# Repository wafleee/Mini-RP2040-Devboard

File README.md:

# Mini RP2040 Devboard

I made a mini devboard that uses the RP2040 as the MCU. It is slightly bigger than the XIAO esp32 s3 but it features 4 extra pins

# Features 
1. ESD protection(protection against electrostatic discharge from body )
2.  Dual-core Arm Cortex-M0+ running up to 133 MHz
3.  18 GPIO pins| 3 ADC pins| GPIO 4- SDA | GPIO 5 - SCL
4.  

# SCHEMATIC

# PCB

# Firmware

No firmware is needed, just hit upload to any sketch on Arduino IDE and it will built itself.

#BOM

| Designator                                     | Footprint                                               | Qty | Value                       | Link                                                                                                                                                               |
| ---------------------------------------------- | ------------------------------------------------------- | --- | --------------------------- | ------------------------------------------------------------------------------------------------------------------------------------------------------------------ |
| C10, C12, C13, C14, C15, C16, C17, C19, C3, C9 | 603                                                     | 10  | 100nF                       | Already owned                                                                                                                                                      |
| C11, C18, C7, C8                               | 603                                                     | 4   | 1µF                         | [Robu](https://robu.in/product/06033d105kat2a-kyocera-avx-cap-smd-mlcc-1-%c2%b5f-25-v-0603-pack-of-1/)                                                             |
| C4, C5                                         | 603                                                     | 2   | 15pF                        | [Robu](https://robu.in/product/0603n150j500ct-walsin-cap-smd-mlcc-15-pf-50-v-0603-pack-of-10/)                                                                     |
| C6                                             | 805                                                     | 1   | 10µF                        | [Robu](https://robu.in/product/cc0805kkx5r8bb106-yageo-cap-smd-mlcc-10-%c2%b5f-25-v-0805-2012-metric10-x5r-cc-series/)                                             |
| D1                                             | LED_WS2812B-2020_PLCC4_2.0x2.0mm                        | 1   | WS2812B-2020                | [Robu](https://robu.in/product/sme-ws2812b-2020-addressable-rgb-pixel-led-worldsemi/)                                                                                                                                                                 |
| D2                                             | 603                                                     | 1   | LED                         | [Robu](https://robu.in/product/19-217-r6c-al1m2vy-3t-everlight-red-528nm-led-indication-discrete-3-3v-0603-1608-metric/)                                           |
| J1                                             | USB_C_Receptacle_GCT_USB4105-xx-A_16P_TopMnt_Horizontal | 1   | USB_C_Receptacle_USB2.0_14P | [Robu](https://robu.in/product/type-c-31-m-12-hroparts-5a-1-16p-female-type-c-smd-usb-connectors-rohs/)                                                            |
| J4, J5                                         | PinHeader_1x10_P2.54mm_Vertical                         | 2   | Conn_01x10_Pin              | [Robu](https://robu.in/product/ds1021-1x10sf11-b-connfly-1x10-pin-2-54mm-pin-header-v-t-type/)                                                                     |
| R1, R2                                         | 603                                                     | 2   | 5.1kΩ                       | [Robu](https://robu.in/product/rt0603fre075k1l-yageo-100mw-thin-film-resistor-75v-%c2%b150ppm-%e2%84%83-%c2%b11-5-1k%cf%89-0603-chip-resistor-surface-mount-rohs/) |
| R3, R6                                         | 603                                                     | 2   | 1kΩ                         | [Robu](https://robu.in/product/1k-ohm-1-4w-0603-surface-mount-chip-resistor-pack-of-100/)                                                                          |
| R4, R5                                         | 603                                                     | 2   | 27Ω                         | [Robu](https://robu.in/product/rc0603jr-0727rl-yageo-smd-chip-resistor-27-ohm-%c2%b1-5-100-mw-0603-1608-metric-thick-film-general-purpose/)                        |
| SW1                                            | SW_SPST_B3U-1000P                                       | 1   | SW_MEC_5G                   | [Robu](https://robu.in/product/1-month-warranty-470/)                                                                                                              |
| U1                                             | QFN-56-1EP_7x7mm_P0.4mm_EP3.2x3.2mm                     | 1   | RP2040                      | [Robu](https://robu.in/product/raspberry-pi-rp2040/)                                                                                                               |
| U3                                             | SOIC-8_5.3x5.3mm_P1.27mm                                | 1   | W25Q128JVS                  | [Lion Circuits](https://www.lioncircuits.com/parts/W25Q128JVSIQ)                                                                                                   |
| U4                                             | SOT-23-5                                                | 1   | AP2112K-3.3                 | [Lion Circuits](https://www.lioncircuits.com/parts/AP2112K-3.3TRG1)                                                                                                |
| U5                                             | SOT-23-6                                                | 1   | USBLC6-2SC6                 | [Robu](https://robu.in/product/usblc6-2sc6-ms-msksemi-4-5a-15v-150w-6v-5v-sot-23-6-esd-and-surge-protection-tvs-esd-rohs/)                                         |
| Y2                                             | Crystal_SMD_Abracon_ABM8AIG-4Pin_3.2x2.5mm              | 1   | Crystal_GND3                | [Robu](https://robu.in/product/cm4012m00008001-huaxindianzi/)                                                                                                      |

# Credits
Kicad - https://www.kicad.org/

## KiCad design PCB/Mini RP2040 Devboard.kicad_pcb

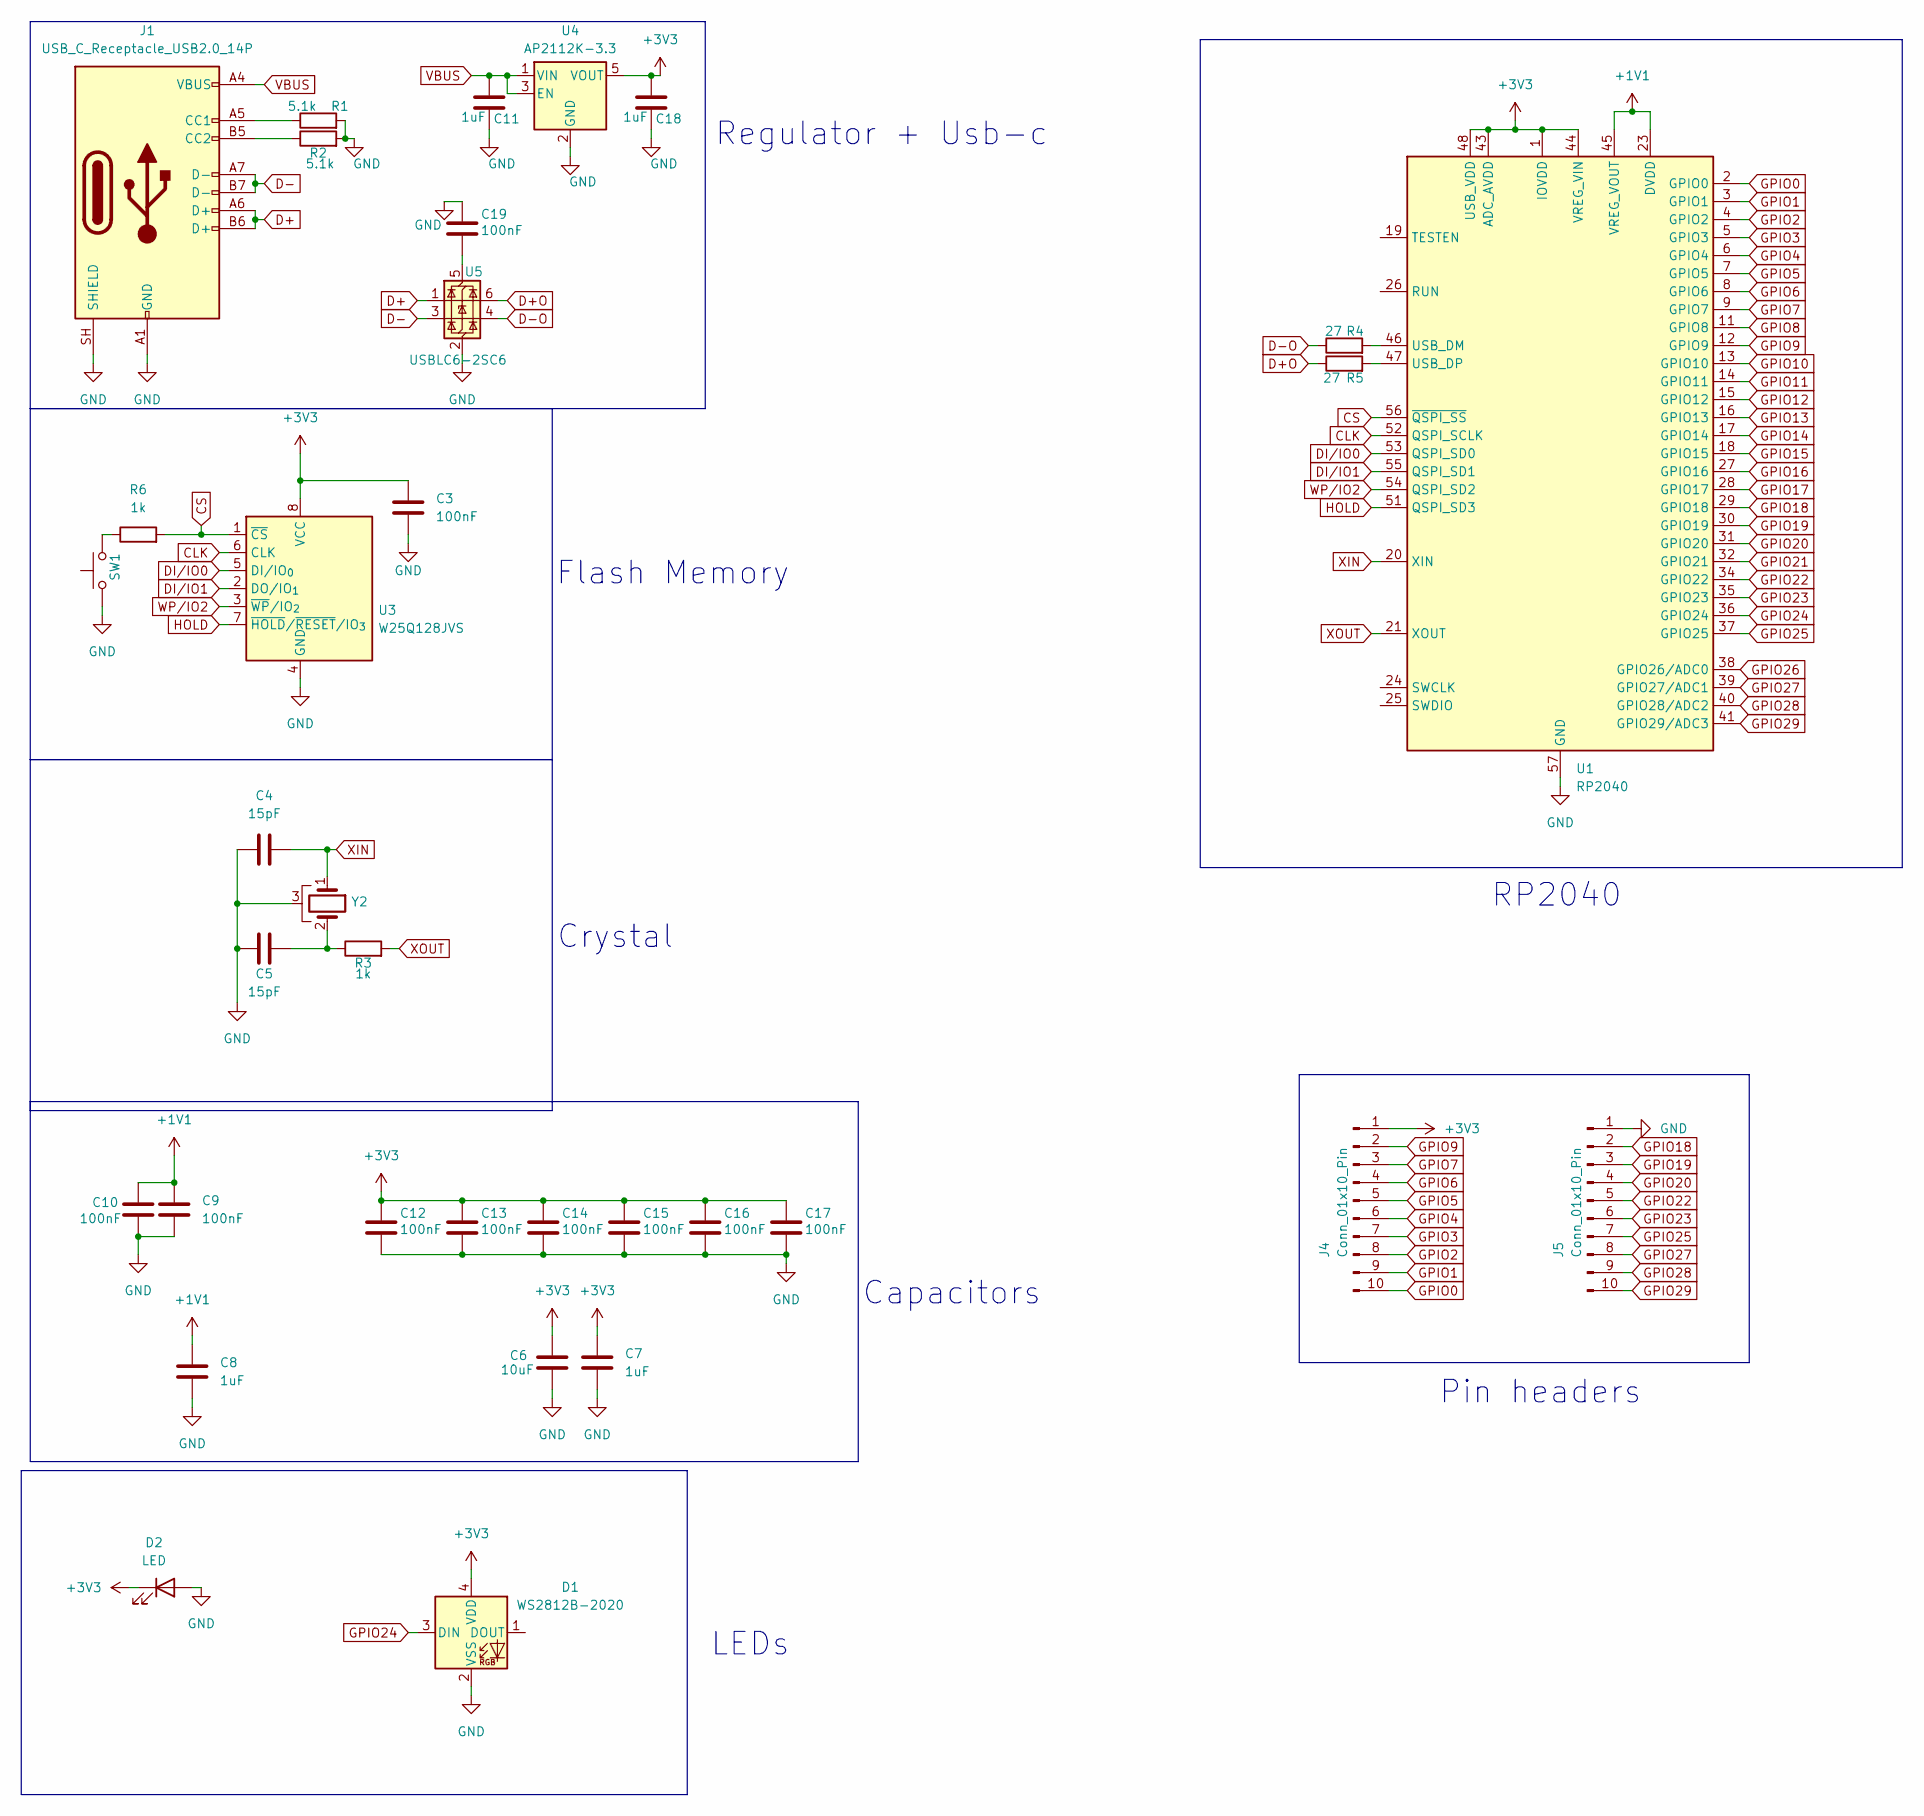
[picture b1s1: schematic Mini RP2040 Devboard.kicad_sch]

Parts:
C3, C9, C10, C12, C13, C14, C15, C16, C17, C19: 100nF; C_0603_1608Metric
C4, C5: 15pF; C_0603_1608Metric
C6: 10uF; C_0805_2012Metric
C7, C8, C11, C18: 1uF; C_0603_1608Metric
D1: WS2812B-2020; LED_WS2812B-2020_PLCC4_2.0x2.0mm
D2: LED; LED_0603_1608Metric
J1: USB_C_Receptacle_USB2.0_14P; USB_C_Receptacle_GCT_USB4105-xx-A_16P_TopMnt_Horizontal
J4, J5: Conn_01x10_Pin; PinHeader_1x10_P2.54mm_Vertical
R1, R2: 5.1k; R_0603_1608Metric
R3, R6: 1k; R_0603_1608Metric
R4, R5: 27; R_0603_1608Metric
SW1: SW_MEC_5G; SW_SPST_B3U-1000P
U1: RP2040; QFN-56-1EP_7x7mm_P0.4mm_EP3.2x3.2mm
U3: W25Q128JVS; SOIC-8_5.3x5.3mm_P1.27mm
U4: AP2112K-3.3; SOT-23-5
U5: USBLC6-2SC6; SOT-23-6
Y2: Crystal_GND3; Crystal_SMD_Abracon_ABM10-4Pin_2.5x2.0mm

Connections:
+1V1: C8.1, C9.1, C10.1, U1.23 (DVDD), U1.45 (VREG_VOUT), U1.50 (DVDD)
+3V3: C3.1, C6.1, C7.1, C12.1, C13.1, C14.1, C15.1, C16.1, C17.1, C18.1, D1.4 (VDD), D2.1 (K), J4.1, U1.1 (IOVDD), U1.10 (IOVDD), U1.22 (IOVDD), U1.33 (IOVDD), U1.42 (IOVDD), U1.43 (ADC_AVDD), U1.44 (VREG_VIN), U1.48 (USB_VDD), U1.49 (IOVDD), U3.8 (VCC), U4.5 (VOUT)
CLK: U1.52 (QSPI_SCLK), U3.6 (CLK)
CS: R6.2, U1.56 (~QSPI_SS), U3.1 (~CS)
D+: J1.A6 (D+), J1.B6 (D+), U5.1 (I/O1)
D+O: R5.1, U5.6 (I/O1)
D-: J1.A7 (D-), J1.B7 (D-), U5.3 (I/O2)
D-O: R4.1, U5.4 (I/O2)
DI/IO0: U1.53 (QSPI_SD0), U3.5 (DI/IO_{0})
DI/IO1: U1.55 (QSPI_SD1), U3.2 (DO/IO_{1})
GPIO0: J4.10, U1.2 (GPIO0)
GPIO1: J4.9, U1.3 (GPIO1)
GPIO2: J4.8, U1.4 (GPIO2)
GPIO3: J4.7, U1.5 (GPIO3)
GPIO4: J4.6, U1.6 (GPIO4)
GPIO5: J4.5, U1.7 (GPIO5)
GPIO6: J4.4, U1.8 (GPIO6)
GPIO7: J4.3, U1.9 (GPIO7)
GPIO8: U1.11 (GPIO8)
GPIO9: J4.2, U1.12 (GPIO9)
GPIO10: U1.13 (GPIO10)
GPIO11: U1.14 (GPIO11)
GPIO12: U1.15 (GPIO12)
GPIO13: U1.16 (GPIO13)
GPIO14: U1.17 (GPIO14)
GPIO15: U1.18 (GPIO15)
GPIO16: U1.27 (GPIO16)
GPIO17: U1.28 (GPIO17)
GPIO18: J5.2, U1.29 (GPIO18)
GPIO19: J5.3, U1.30 (GPIO19)
GPIO20: J5.4, U1.31 (GPIO20)
GPIO21: U1.32 (GPIO21)
GPIO22: J5.5, U1.34 (GPIO22)
GPIO23: J5.6, U1.35 (GPIO23)
GPIO24: D1.3 (DIN), U1.36 (GPIO24)
GPIO25: J5.7, U1.37 (GPIO25)
GPIO26: U1.38 (GPIO26/ADC0)
GPIO27: J5.8, U1.39 (GPIO27/ADC1)
GPIO28: J5.9, U1.40 (GPIO28/ADC2)
GPIO29: J5.10, U1.41 (GPIO29/ADC3)
HOLD: U1.51 (QSPI_SD3), U3.7 (~HOLD/~RESET/IO_{3})
unnamed: C5.2, R3.1, Y2.2
unnamed: J1.A5 (CC1), R1.1
unnamed: J1.B5 (CC2), R2.1
unnamed: R4.2, U1.46 (USB_DM)
unnamed: R5.2, U1.47 (USB_DP)
unnamed: C19.2, U5.5 (VBUS)
VBUS: C11.1, J1.A4 (VBUS), J1.A9 (VBUS), J1.B4 (VBUS), J1.B9 (VBUS), U4.1 (VIN), U4.3 (EN)
WP/IO2: U1.54 (QSPI_SD2), U3.3 (~WP/IO_{2})
XIN: C4.2, U1.20 (XIN), Y2.1
XOUT: R3.2, U1.21 (XOUT)

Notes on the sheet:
Capacitors
Flash Memory
LEDs
Crystal
Regulator + Usb-c
Pin headers
RP2040

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
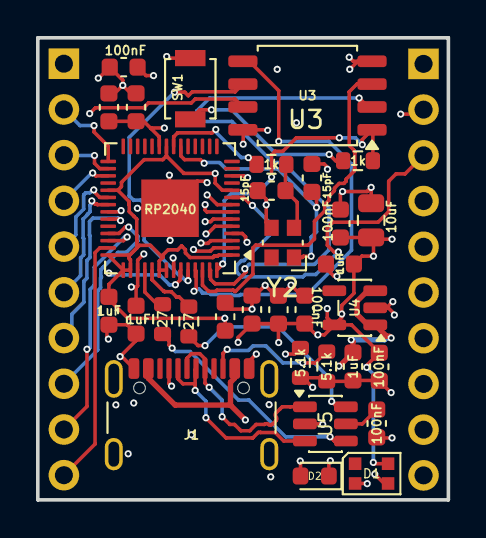
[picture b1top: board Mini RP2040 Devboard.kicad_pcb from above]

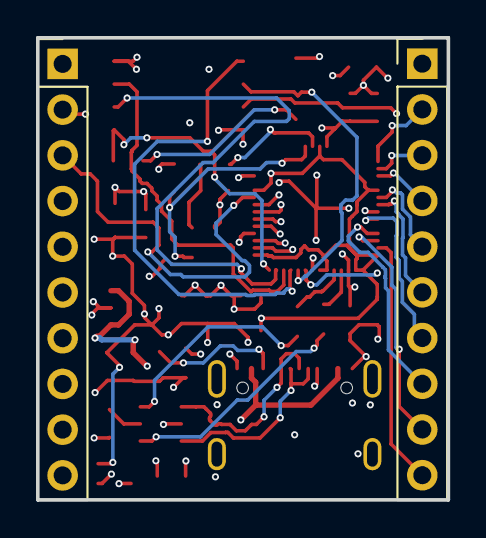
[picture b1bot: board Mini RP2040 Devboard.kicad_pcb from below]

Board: 4 copper layers, 22.8 x 25.7 mm, 34 parts (2 on the bottom side), 42 nets.

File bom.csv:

Designator,Footprint,Quantity,Value,LINK
"C10, C12, C13, C14, C15, C16, C17, C19, C3, C9",603,10,100nF,Already owned
"C11, C18, C7, C8",603,4,1uF,https://robu.in/product/06033d105kat2a-kyocera-avx-cap-smd-m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
"C4, C5",603,2,15pF,https://robu.in/product/0603n150j500ct-walsin-cap-smd-mlcc-1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
C6,805,1,10uF,https://robu.in/product/cc0805kkx5r8bb106-yageo-cap-smd-mlcc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
D1,LED_WS2812B-2020_PLCC4_2.0x2.0mm,1,WS2812B-2020,
D2,603,1,LED,https://robu.in/product/19-217-r6c-al1m2vy-3t-everlight-red-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
J1,USB_C_Receptacle_GCT_USB4105-xx-A_16P_TopMnt_Horizontal,1,USB_C_Receptacle_USB2.0_14P,https://robu.in/product/type-c-31-m-12-hroparts-5a-1-16p-fem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
"J4, J5",PinHeader_1x10_P2.54mm_Vertical,2,Conn_01x10_Pin,https://robu.in/product/ds1021-1x10sf11-b-connfly-1x10-pin-2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
"R1, R2",603,2,5.1k,https://robu.in/product/rt0603fre075k1l-yageo-100mw-thin-fil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
"R3, R6",603,2,1k,https://robu.in/product/1k-ohm-1-4w-0603-surface-mount-chip-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
"R4, R5",603,2,27,https://robu.in/product/rc0603jr-0727rl-yageo-smd-chip-resis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
SW1,SW_SPST_B3U-1000P,1,SW_MEC_5G,https://robu.in/product/1-month-warranty-470/
U1,QFN-56-1EP_7x7mm_P0.4mm_EP3.2x3.2mm,1,RP2040,https://robu.in/product/raspberry-pi-rp2040/
U3,SOIC-8_5.3x5.3mm_P1.27mm,1,W25Q128JVS,https://www.lioncircuits.com/parts/W25Q128JVSIQ
U4,SOT-23-5,1,AP2112K-3.3,https://www.lioncircuits.com/parts/AP2112K-3.3TRG1?srsltid=A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
U5,SOT-23-6,1,USBLC6-2SC6,https://robu.in/product/usblc6-2sc6-ms-msksemi-4-5a-15v-150w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
Y2,Crystal_SMD_Abracon_ABM8AIG-4Pin_3.2x2.5mm,1,Crystal_GND3,https://robu.in/product/cm4012m00008001-huaxindianzi/
